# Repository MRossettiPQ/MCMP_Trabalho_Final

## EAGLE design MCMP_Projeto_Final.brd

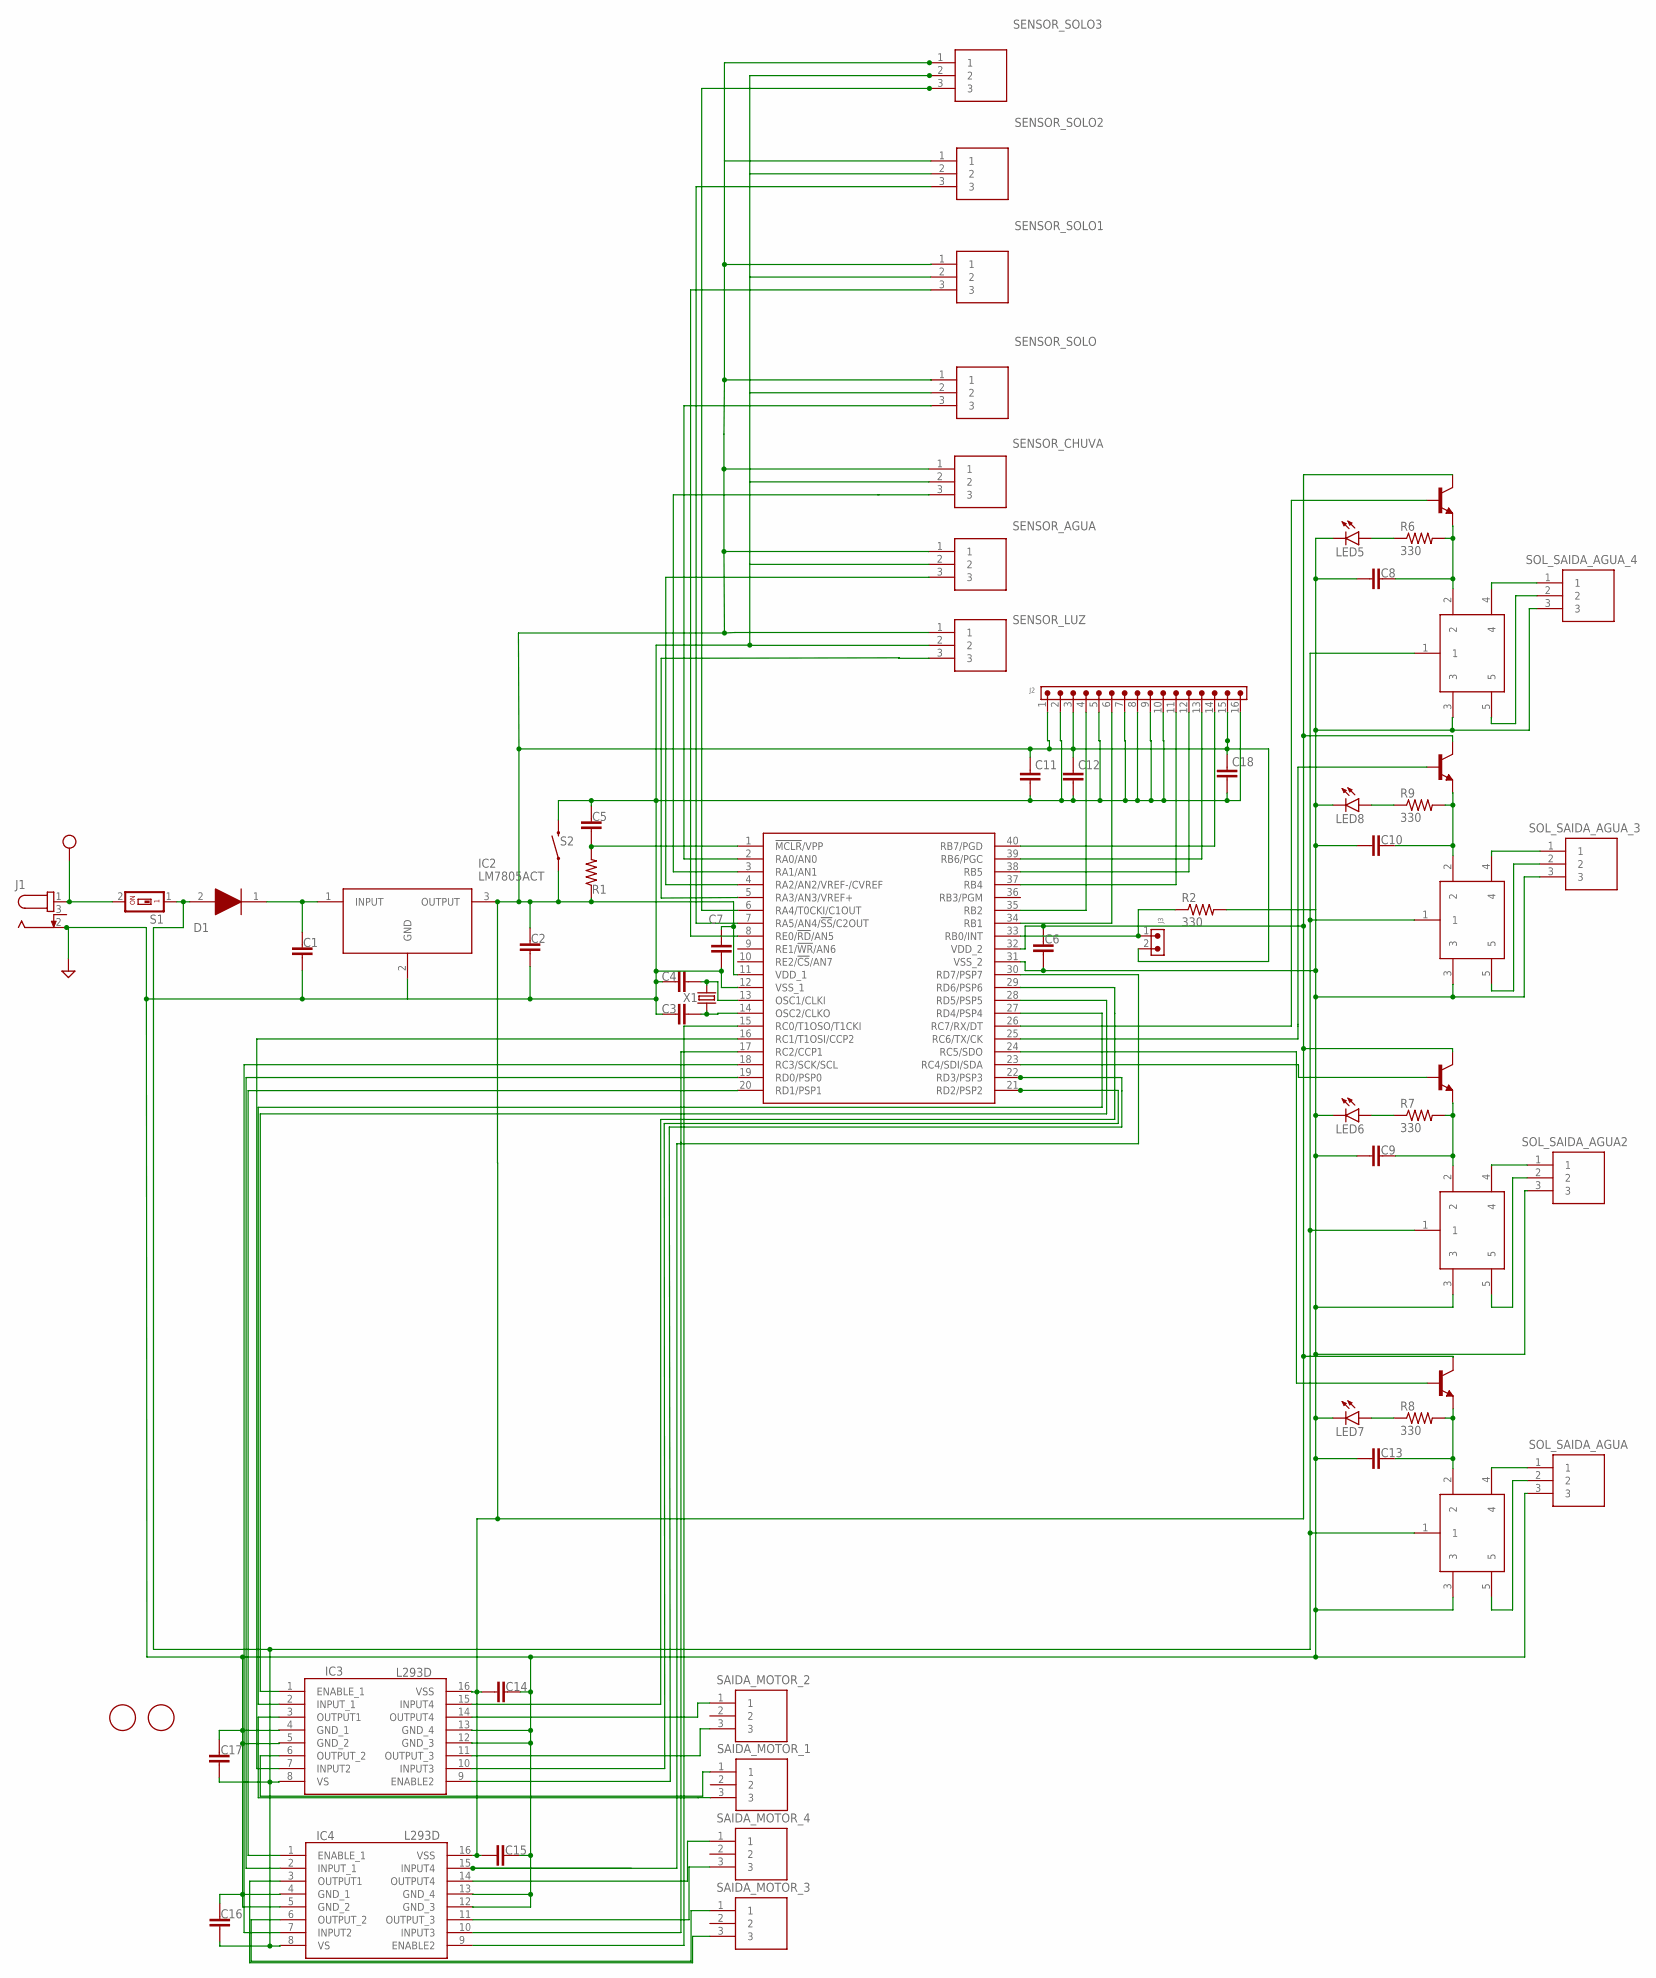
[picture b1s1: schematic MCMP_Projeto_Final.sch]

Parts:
C1: 470uF; CAP_0805
C2: 1uF; CAP_0805
C3, C4: 33p; CAP_0805
C5, C6, C7, C8, C9, C10, C11, C12, C13, C18: 10u; CAP_0805
C14, C15: 0.1u; CAP_0805
C16, C17: 100u; CAP_0805
D1: 1N4007S; DIOAD1470W65L470D250
IC1: PIC16F877A-I_P; DIP1550W56P254L5219H483Q40N
IC2: LM7805ACT; TO254P470X1016X2019-3P
IC3, IC4: L293D; DIP880W50P254L2000H510Q16N
J1: 694106301002
J2: 6130XX11121_61301611121; 61301611121
J3: 6200XX11121_62000211121; 62000211121
K1, K2, K3, K5: SRD-05VDC-SL-C; SRD
LED5, LED6, LED7, LED8: LEDCHIPLED_0805; CHIPLED_0805
Q1, Q2, Q3, Q5: 2N1711; TO39
R1: 10k; RES_0805
R2, R6, R7, R8, R9: 330; RES_0805
S1: SWS001; SMS-001
S2: MOMENTARY-SWITCH-SPST-PTH-6.0MM; TACTILE_SWITCH_PTH_6.0MM
SAIDA_MOTOR_1, SAIDA_MOTOR_2, SAIDA_MOTOR_3, SAIDA_MOTOR_4: TB005-762-03BE; SHDR3W100P0X762_1X3_2286X1260X
SENSOR_AGUA: TB005-762-03BE; SHDR3W100P0X762_1X3_2286X1260X
SENSOR_CHUVA: TB005-762-03BE; SHDR3W100P0X762_1X3_2286X1260X
SENSOR_LUZ: TB005-762-03BE; SHDR3W100P0X762_1X3_2286X1260X
SENSOR_SOLO, SENSOR_SOLO1, SENSOR_SOLO2, SENSOR_SOLO3: TB005-762-03BE; SHDR3W100P0X762_1X3_2286X1260X
SOL_SAIDA_AGUA, SOL_SAIDA_AGUA2: TB005-762-03BE; SHDR3W100P0X762_1X3_2286X1260X
SOL_SAIDA_AGUA_3, SOL_SAIDA_AGUA_4: TB005-762-03BE; SHDR3W100P0X762_1X3_2286X1260X
U$5, U$6: FIDUCIAL; FIDUCIAL_1MM
X1: 4Mhz; 5032/2P

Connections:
ACIONA_BOBINA_1: IC1.24 (RC5/SDO), Q5.2 (B)
ACIONA_BOBINA_2: IC1.23 (RC4/SDI/SDA), Q2.2 (B)
ACIONA_BOBINA_3: IC1.25 (RC6/TX/CK), Q3.2 (B)
ACIONA_BOBINA_4: IC1.26 (RC7/RX/DT), Q1.2 (B)
ENABLE_MOTOR_1: IC1.28 (RD5/PSP5), IC3.1 (ENABLE_1)
ENABLE_MOTOR_2: IC1.22 (RD3/PSP3), IC3.9 (ENABLE2)
ENABLE_MOTOR_3: IC1.20 (RD1/PSP1), IC4.1 (ENABLE_1)
ENABLE_MOTOR_4: IC1.15 (RC0/T1OSO/T1CKI), IC4.9 (ENABLE2)
GND: C1.2, C2.2, C3.1, C4.1, C5.1, C6.2, C7.2, C8.2, C9.2, C10.2, C11.2, C12.2, C13.2, C14.2, C15.1, C16.1, C17.1, C18.2, IC1.12 (VSS_1), IC1.31 (VSS_2), IC2.2 (GND), IC3.4 (GND_1), IC3.5 (GND_2), IC3.12 (GND_3), IC3.13 (GND_4), IC4.4 (GND_1), IC4.5 (GND_2), IC4.12 (GND_3), IC4.13 (GND_4), J1.2, J2.2, J2.5, J2.7, J2.8, J2.9, J2.10, J2.16, K1.3, K2.3, K3.3, K5.3, LED5.C, LED6.C, LED7.C, LED8.C, R2.2, S2.3 (2), SENSOR_AGUA.2, SENSOR_CHUVA.2, SENSOR_LUZ.2, SENSOR_SOLO.2, SENSOR_SOLO1.2, SENSOR_SOLO2.2, SENSOR_SOLO3.2, SOL_SAIDA_AGUA.3, SOL_SAIDA_AGUA2.3, SOL_SAIDA_AGUA_3.3, SOL_SAIDA_AGUA_4.3
INPUT1_MOTOR_1: IC1.27 (RD4/PSP4), IC3.2 (INPUT_1)
INPUT1_MOTOR_2: IC1.21 (RD2/PSP2), IC3.10 (INPUT3)
INPUT1_MOTOR_3: IC1.19 (RD0/PSP0), IC4.2 (INPUT_1)
INPUT1_MOTOR_4: IC1.17 (RC2/CCP1), IC4.10 (INPUT3)
INPUT2_MOTOR_2: IC1.29 (RD6/PSP6), IC3.15 (INPUT4)
INPUT2_MOTOR_3: IC1.18 (RC3/SCK/SCL), IC4.7 (INPUT2)
INPUT2_MOTOR_4: IC1.30 (RD7/PSP7), IC4.15 (INPUT4)
INPUT2_MOTO_1: IC1.16 (RC1/T1OSI/CCP2), IC3.7 (INPUT2)
unnamed: C1.1, D1.1 (K), IC2.1 (INPUT)
unnamed: IC1.8 (RE0/!RD!/AN5), SENSOR_SOLO1.3
unnamed: IC1.7 (RA5/AN4/!SS!/C2OUT), SENSOR_SOLO2.3
unnamed: C5.2, IC1.1 (!MCLR!/VPP), R1.2
unnamed: C4.2, IC1.13 (OSC1/CLKI), X1.2
unnamed: C3.2, IC1.14 (OSC2/CLKO), X1.1
unnamed: IC1.2 (RA0/AN0), SENSOR_SOLO.3
unnamed: K5.4, SOL_SAIDA_AGUA.1
unnamed: IC1.6 (RA4/T0CKI/C1OUT), SENSOR_SOLO3.3
unnamed: IC1.33 (RB0/INT), J3.1, R2.1
unnamed: IC1.3 (RA1/AN1), SENSOR_CHUVA.3
unnamed: IC1.4 (RA2/AN2/VREF-/CVREF), SENSOR_AGUA.3
unnamed: K1.4, SOL_SAIDA_AGUA_4.1
unnamed: LED8.A, R9.1
unnamed: LED5.A, R6.1
unnamed: C8.1, K1.2, Q1.1 (E), R6.2
unnamed: K1.5, SOL_SAIDA_AGUA_4.2
unnamed: C13.1, K5.2, Q5.1 (E), R8.2
unnamed: K5.5, SOL_SAIDA_AGUA.2
unnamed: C10.1, K3.2, Q3.1 (E), R9.2
unnamed: LED6.A, R7.1
unnamed: C9.1, K2.2, Q2.1 (E), R7.2
unnamed: K2.4, SOL_SAIDA_AGUA2.1
unnamed: K2.5, SOL_SAIDA_AGUA2.2
unnamed: LED7.A, R8.1
unnamed: K3.4, SOL_SAIDA_AGUA_3.1
unnamed: K3.5, SOL_SAIDA_AGUA_3.2
unnamed: IC1.5 (RA3/AN3/VREF+), SENSOR_LUZ.3
OUTPUT1_MOTOR_1: IC3.3 (OUTPUT1), SAIDA_MOTOR_1.3
OUTPUT1_MOTOR_2: IC3.11 (OUTPUT_3), SAIDA_MOTOR_2.3
OUTPUT1_MOTOR_3: IC4.3 (OUTPUT1), SAIDA_MOTOR_3.3
OUTPUT1_MOTOR_4: IC4.11 (OUTPUT_3), SAIDA_MOTOR_4.3
OUTPUT2_MOTOR_1: IC3.6 (OUTPUT_2), SAIDA_MOTOR_1.1
OUTPUT2_MOTOR_2: IC3.14 (OUTPUT4), SAIDA_MOTOR_2.1
OUTPUT2_MOTOR_3: IC4.6 (OUTPUT_2), SAIDA_MOTOR_3.1
OUTPUT2_MOTOR_4: IC4.14 (OUTPUT4), SAIDA_MOTOR_4.1
RB1: IC1.34 (RB1), J2.6
RB2: IC1.35 (RB2), J2.4
RB4: IC1.37 (RB4), J2.11
RB5: IC1.38 (RB5), J2.12
RB6: IC1.39 (RB6/PGC), J2.13
RB7: IC1.40 (RB7/PGD), J2.14
VCC: J1.1, S1.2
VCC5: C2.1, C6.1, C7.1, C11.1, C12.1, C14.1, C15.2, C18.1, IC1.11 (VDD_1), IC1.32 (VDD_2), IC2.3 (OUTPUT), IC3.16 (VSS), IC4.16 (VSS), J2.1, J2.3, J2.15, J3.2, Q1.3 (C), Q2.3 (C), Q3.3 (C), Q5.3 (C), R1.1, S2.1, SENSOR_AGUA.1, SENSOR_CHUVA.1, SENSOR_LUZ.1, SENSOR_SOLO.1, SENSOR_SOLO1.1, SENSOR_SOLO2.1, SENSOR_SOLO3.1
VCC12: C16.2, C17.2, D1.2 (A), IC3.8 (VS), IC4.8 (VS), K1.1, K2.1, K3.1, K5.1, S1.1

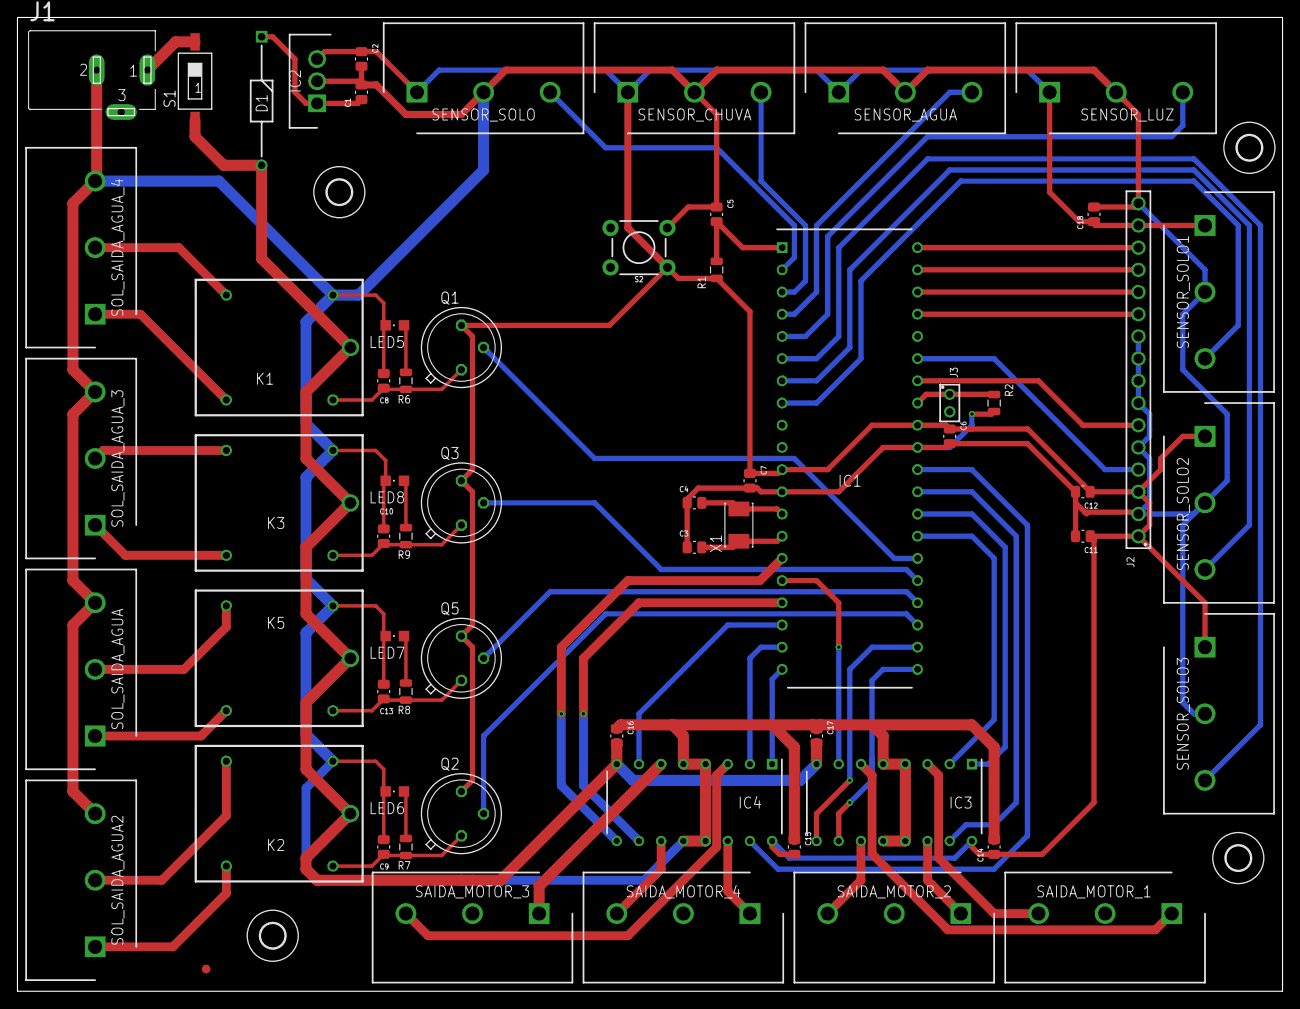
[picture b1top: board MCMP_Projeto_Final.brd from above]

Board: 2 copper layers, 144.8 x 111.4 mm, 68 parts (1 on the bottom side), 62 nets.

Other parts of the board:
U$1, U$2, U$3, U$4: 2,8

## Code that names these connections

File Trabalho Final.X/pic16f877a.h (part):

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
extern __at(0x0005) volatile __PORTAbits_t PORTAbits;

#define _RA0                    0x01
#define _RA1                    0x02
#define _RA2                    0x04
#define _RA3                    0x08
#define _RA4                    0x10
#define _RA5                    0x20

//==============================================================================

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
extern __at(0x0006) volatile __PORTBbits_t PORTBbits;

#define _RB0                    0x01
#define _RB1                    0x02
#define _RB2                    0x04
#define _RB3                    0x08
#define _RB4                    0x10
#define _RB5                    0x20
#define _RB6                    0x40
#define _RB7                    0x80

//==============================================================================

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
extern __at(0x0007) volatile __PORTCbits_t PORTCbits;

#define _RC0                    0x01
#define _RC1                    0x02
#define _RC2                    0x04
#define _RC3                    0x08
#define _RC4                    0x10
#define _RC5                    0x20
#define _RC6                    0x40
#define _RC7                    0x80

//==============================================================================

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
extern __at(0x0008) volatile __PORTDbits_t PORTDbits;

#define _RD0                    0x01
#define _RD1                    0x02
#define _RD2                    0x04
#define _RD3                    0x08
#define _RD4                    0x10
#define _RD5                    0x20
#define _RD6                    0x40
#define _RD7                    0x80

//==============================================================================

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
extern __at(0x0009) volatile __PORTEbits_t PORTEbits;

#define _RE0                    0x01
#define _RE1                    0x02
#define _RE2                    0x04

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#define _WRT_1FOURTH            0x3BFF  // 0000h to 07FFh write-protected; 0800h to 1FFFh may be written to by EECON control.
#define _WRT_256                0x3DFF  // 0000h to 00FFh write-protected; 0100h to 1FFFh may be written to by EECON control.
#define _WRT_OFF                0x3FFF  // Write protection off; all program memory may be written to by EECON control.
#define _DEBUG_ON               0x37FF  // In-Circuit Debugger enabled, RB6 and RB7 are dedicated to the debugger.
#define _DEBUG_OFF              0x3FFF  // In-Circuit Debugger disabled, RB6 and RB7 are general purpose I/O pins.
#define _CP_ON                  0x1FFF  // All program memory code-protected.
#define _CP_ALL                 0x1FFF  // All program memory code-protected.
#define _CP_OFF                 0x3FFF  // Code protection off.
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#define EEIF                    PIR2bits.EEIF                   // bit 4
#define CMIF                    PIR2bits.CMIF                   // bit 6

#define RA0                     PORTAbits.RA0                   // bit 0
#define RA1                     PORTAbits.RA1                   // bit 1
#define RA2                     PORTAbits.RA2                   // bit 2
#define RA3                     PORTAbits.RA3                   // bit 3
#define RA4                     PORTAbits.RA4                   // bit 4
#define RA5                     PORTAbits.RA5                   // bit 5

#define RB0                     PORTBbits.RB0                   // bit 0
#define RB1                     PORTBbits.RB1                   // bit 1
#define RB2                     PORTBbits.RB2                   // bit 2
#define RB3                     PORTBbits.RB3                   // bit 3
#define RB4                     PORTBbits.RB4                   // bit 4
#define RB5                     PORTBbits.RB5                   // bit 5
#define RB6                     PORTBbits.RB6                   // bit 6
#define RB7                     PORTBbits.RB7                   // bit 7

#define RC0                     PORTCbits.RC0                   // bit 0
#define RC1                     PORTCbits.RC1                   // bit 1
#define RC2                     PORTCbits.RC2                   // bit 2
#define RC3                     PORTCbits.RC3                   // bit 3
#define RC4                     PORTCbits.RC4                   // bit 4
#define RC5                     PORTCbits.RC5                   // bit 5
#define RC6                     PORTCbits.RC6                   // bit 6
#define RC7                     PORTCbits.RC7                   // bit 7

#define RD0                     PORTDbits.RD0                   // bit 0
#define RD1                     PORTDbits.RD1                   // bit 1
#define RD2                     PORTDbits.RD2                   // bit 2
#define RD3                     PORTDbits.RD3                   // bit 3
#define RD4                     PORTDbits.RD4                   // bit 4
#define RD5                     PORTDbits.RD5                   // bit 5
#define RD6                     PORTDbits.RD6                   // bit 6
#define RD7                     PORTDbits.RD7                   // bit 7

#define RE0                     PORTEbits.RE0                   // bit 0
#define RE1                     PORTEbits.RE1                   // bit 1
#define RE2                     PORTEbits.RE2                   // bit 2

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
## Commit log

2021-05-05 0.0.0.050520211412
2021-05-05 0.0.0.050520211419
2021-05-05 0.0.0.050520211742
2021-05-05 0.0.0.050520211857
2021-05-06 0.0.0.050520212132
2021-05-06 0.0.0.050520212140
2021-05-06 1.0.0.060520210411
2021-05-07 1.07052021.2031
2021-05-07 1.07052021.2032
2021-05-07 1.07052021.2034
2021-05-08 1.08052021.0023
2021-05-08 2.08052021.2018
    Refinamento logica de acionamento
2021-05-09 2.08052021.2125

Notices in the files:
Trabalho Final.X/pic16f877a.h:
SDCC is licensed under the GNU Public license (GPL) v2. Note that
with the GPL. Pic device libraries and header files are located at
parts and their libraries:
SparkFun-Switches: Licensing: Creative Commons ShareAlike 4.0 International - https://creativecommons.org/licenses/by-sa/4.0
Wurth_Connectors_WR-PHD: Copyright: Würth Elektronik
